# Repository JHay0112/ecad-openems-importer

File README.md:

# ECAD OpenEMS Importer

This repository contains a rudimentary application for importing PCB files from an ECAD tool into
OpenEMS. At the moment, I'm just experimenting and targeting KiCAD7 and OpenEMS in particular.
However, I am aiming to leave the interfaces to the ECAD application and the EMS application as
broad as possible so it's not too hard to change in the future. 

At the moment there is enough functionality between the KiCAD interface and the test script to
import the rough outline of a PCB and approximate the shape of some of the traces on the board
in OpenEMS. This is enough to show that the idea is solid, but not enough to do anything very useful
with without a lot of manual work. Once the application is mature it should be able to function as a
simple intermediary for bringing a PCB design into OpenEMS and automatically generating a suitable
mesh.

## Roadmap

For KiCAD 7/8:

- [x] Produce polygons describing continuous copper areas on all layers.
      (Ideally single polygon per area.)
- [x] Produce vias and plated through holes at prescribed positions that provide electrical
      connection and air gap in the middle.
- [ ] Improve meshing beyond automatic utility provided by openEMS and guess/check.

Note: The completed goals have been validated on `examples/kicad7/ti_ant.kicad_pcb` and are only
ready as a prototype.

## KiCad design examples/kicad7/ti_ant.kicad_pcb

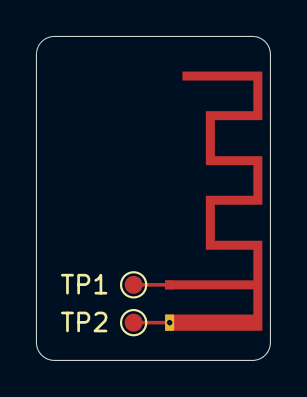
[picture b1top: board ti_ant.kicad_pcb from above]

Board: 2 copper layers, 13.0 x 18.0 mm, 3 parts (0 on the bottom side), 2 nets.

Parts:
AE1: Antenna_Dipole; Texas_SWRA117D_2.4GHz_Left
TP1, TP2: TestPoint; TestPoint_Pad_D1.0mm

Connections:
GND: AE1.2, TP2.1
unnamed: AE1.1, TP1.1

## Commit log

2024-10-28 Add README
2024-10-28 Add circles to end of line segments to round-off properly
2024-10-28 Add basic footprint shapes to copper
2024-10-28 Add handling for compound shapes
2024-10-28 Add basic footprint handling
2024-10-28 Remove pads from current export setup
2024-10-28 Bring zones, segments, and pads into a single feature class
2024-10-30 Add centres to shapes
2024-10-30 Extend test script to add source based upon test point references
2024-10-30 Simplify test model
2024-10-30 Add some pretty naive meshing code and ignore output directory
2024-10-30 Add padding to simulation box
2024-10-31 Tweak padding and ensure unique priorities
2024-11-08 Refactor ecad_intf to use a single polygon to describe a copper layer
2024-11-08 Remove old features from KiCAD 7
2024-11-08 Produce layer polygons from KiCAD description
2024-11-08 Use shapely to perform polygon merger where necessary
2024-11-08 Ditch no longer used shape libraries
2024-11-08 Finalise pad details and setup test script to simulate
2024-11-08 Add roadmap to README
2024-11-09 Move ti_ant.kicad_pcb into examples directory
2024-11-09 Approximate vias/plated through holes as continuous cylinders
2024-11-09 Update progress in README
2024-11-09 Use much larger test mesh on smaller volume
